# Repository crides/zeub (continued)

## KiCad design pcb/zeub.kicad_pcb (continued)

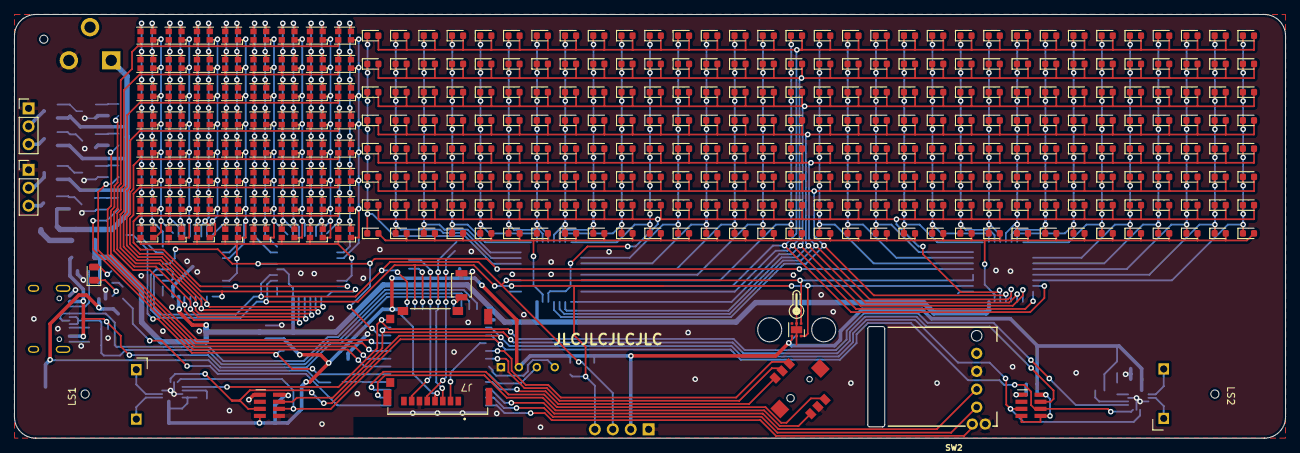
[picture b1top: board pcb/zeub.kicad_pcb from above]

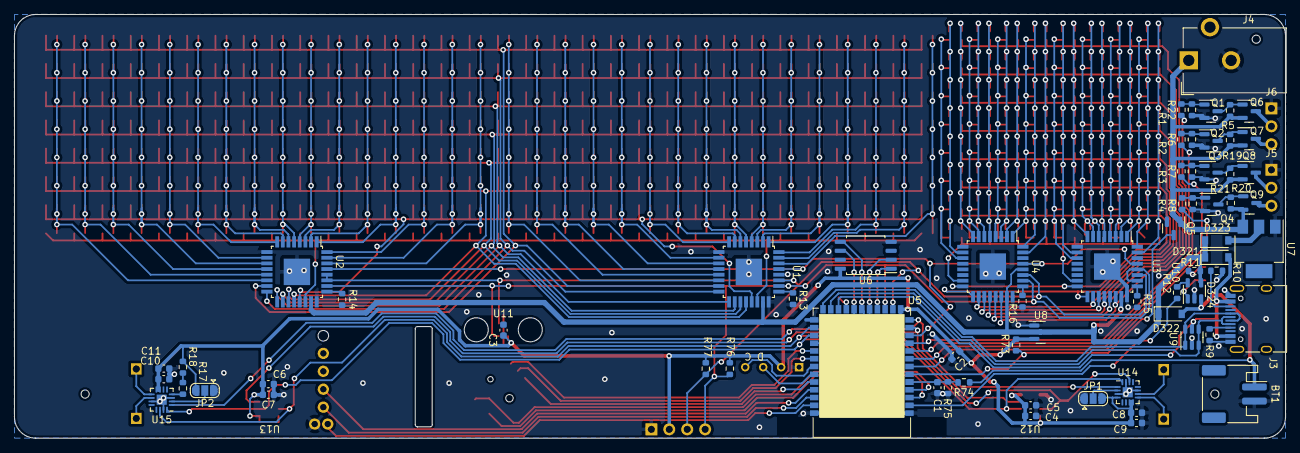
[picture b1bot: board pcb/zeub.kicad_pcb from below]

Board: 2 copper layers, 180.0 x 60.0 mm, 401 parts (68 on the bottom side), 140 nets.

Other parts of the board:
C4, C6: 10uF; C_0603_1608Metric
C5, C7: 0.1uF; C_0603_1608Metric
U12, U13: CMM4030D; CMM4030D_hand_solder

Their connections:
+3V3: C4.2, C5.2, C6.2, C7.2, U12.4 (EN), U12.8 (VDD), U13.4 (EN), U13.5 (~L/R), U13.8 (VDD); also elsewhere on the board
BCLK: U12.6 (SCK), U13.6 (SCK); also elsewhere on the board
GND: C4.1, C5.1, C6.1, C7.1, U12.1 (GND), U12.5 (~L/R), U13.1 (GND); also elsewhere on the board
LRCLK: U12.3 (WS), U13.3 (WS); also elsewhere on the board
SDIN: U12.7 (SD), U13.7 (SD); also elsewhere on the board

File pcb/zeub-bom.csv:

Comment,Designator,Footprint,LCSC Part #
white,"D196,D219,D218,D232,D151,D252,D87,D47,D178,D34,D247,D226,D224,D17,D203,D173,D122,D249,D159,D105,D213,D5,D185,D130,D223,D78,D82,D80,D192,D229,D33,D85,D141,D157,D106,D188,D212,D75,D97,D123,D107,D128,D124,D190,D177,D149,D231,D64,D246,D191,D95,D20,D15,D50,D8,D182,D139,D170,D99,D215,D186,D21,D176,D152,D146,D202,D84,D76,D255,D81,D132,D110,D58,D145,D28,D40,D91,D240,D13,D38,D180,D25,D169,D148,D245,D133,D57,D52,D125,D221,D204,D181,D239,D134,D94,D155,D115,D136,D137,D22,D129,D216,D201,D10,D193,D93,D230,D164,D111,D197,D61,D51,D241,D39,D127,D103,D194,D62,D4,D183,D98,D114,D256,D206,D77,D23,D236,D2,D89,D150,D187,D7,D120,D90,D69,D154,D79,D65,D83,D54,D117,D222,D119,D248,D67,D68,D43,D244,D121,D37,D220,D92,D53,D205,D36,D211,D199,D3,D243,D158,D214,D70,D30,D156,D160,D45,D210,D66,D162,D109,D166,D44,D104,D59,D12,D88,D147,D113,D250,D56,D254,D48,D165,D72,D71,D238,D73,D200,D237,D161,D74,D86,D126,D29,D46,D163,D131,D195,D171,D31,D233,D143,D26,D1,D41,D101,D19,D112,D27,D138,D234,D175,D18,D174,D168,D207,D11,D118,D16,D108,D225,D172,D184,D116,D242,D32,D63,D96,D102,D228,D49,D42,D153,D100,D140,D60,D14,D217,D179,D208,D35,D198,D55,D167,D253,D144,D209,D135,D9,D142,D227,D189,D24,D235,D6,D251",D_0603_1608Metric,
LED_BGRA,"D290,D263,D311,D301,D291,D268,D260,D277,D298,D280,D302,D312,D283,D292,D273,D282,D320,D261,D270,D262,D276,D319,D266,D274,D281,D297,D278,D287,D310,D315,D300,D318,D303,D265,D296,D286,D289,D272,D288,D294,D308,D285,D279,D293,D316,D259,D313,D258,D257,D269,D284,D275,D317,D295,D314,D271,D307,D267,D264,D309,D305,D306,D299,D304",LED_ASMB-KTF0-0A306,
CMM4030D,"U13,U12",CMM4030D_hand_solder,
Conn_01x03,"J5,J6",PinHeader_1x03_P2.54mm_Vertical,
SKRHA,SW1,SKRHA-boss,
LED,D324,D_0805_2012Metric,
TMP117,U11,WSON-6-1EP_2x2mm_P0.65mm_EP1x1.6mm,
Speaker,"LS2,LS1",CMS1609,
RotaryEncoder_Switch,SW2,EVQWGD001,
SW_Push,SW3,SW_SPST_B3U-1000P,
Micro_SD_Card_Det,J7,molex-503182-1852,
OLED-128x32,J2,OLED-128x64,
5.1k,"R10,R9",R_0603_1608Metric,
AO3400A,"Q4,Q1,Q5,Q2,Q3",SOT-23,
100,"R3,R2,R1,R4",R_0603_1608Metric,
MAX98357A,"U15,U14",QFN-16-1EP_3x3mm_P0.5mm_EP1.45x1.45mm,
10nF,C1,C_0603_1608Metric,
AO3401A,"Q6,Q9,Q7,Q8",SOT-23,
100k,"R18,R8,R22,R6,R7,R17,R73",R_0603_1608Metric,
SRV05-4,U9,SOT-23-6,
0.1uF,"C10,C7,C8,C3,C5",C_0603_1608Metric,
IS31FL3729,"U2,U1,U4,U3",eTQFP-32_7x7mm_P0.8mm,
10k,"R19,R12,R21,R20,R16,R5,R13,R14,R15",R_0603_1608Metric,
10uF,"C9,C4,C11,C6",C_0603_1608Metric,
2.2k,"R77,R76",R_0603_1608Metric,
SolderJumper_3_Open,"JP1,JP2",SolderJumper-3_P1.3mm_Open_RoundedPad1.0x1.5mm,
LTC4054ES5-4.2,U10,TSOT-23-5,
1k,R11,R_0603_1608Metric,
holyiot-18010-no-underside,U5,holyiot-18010-no-underside,
TLV1117-50,U7,SOT-223,
1uF,C2,C_0603_1608Metric,
USB_C_Receptacle_USB2.0,J3,USB_C_Receptacle_HRO_TYPE-C-31-M-12,
5.1M,"R75,R74",R_0603_1608Metric,
D_Schottky,"D323,D321,D322",D_SOD-123,
MT25QL128ABA1ESE,U6,SOIC-8_5.23x5.23mm_P1.27mm,
Barrel_Jack_Switch,J4,BarrelJack_CUI_PJ-102AH_Horizontal,
XC6206PxxxMR,U8,SOT-23,
Battery_Cell,BT1,JST_PH_S2B-PH-SM4-TB_1x02-1MP_P2.00mm_Horizontal,

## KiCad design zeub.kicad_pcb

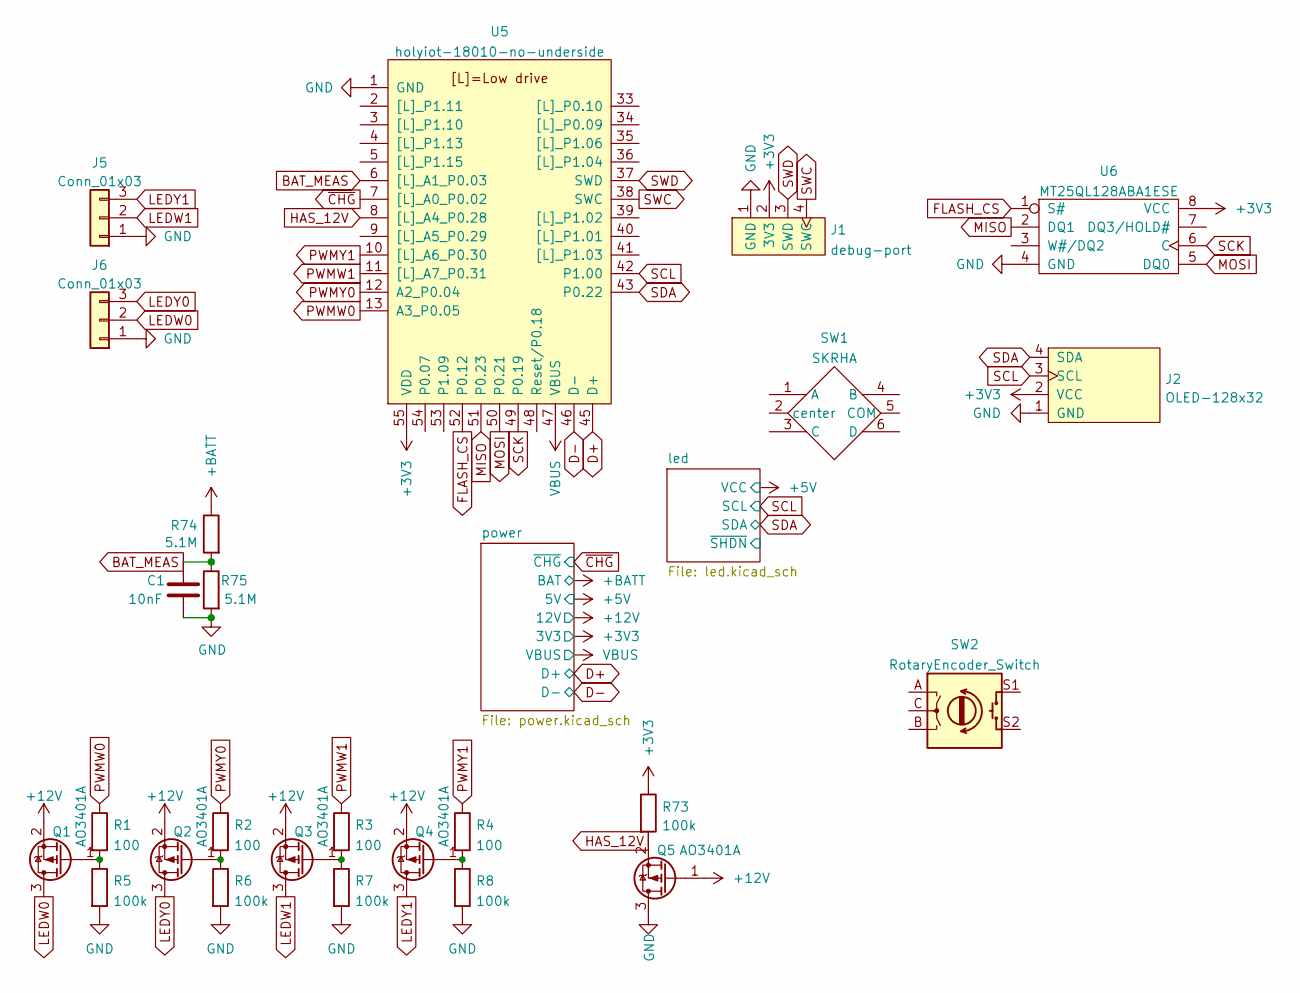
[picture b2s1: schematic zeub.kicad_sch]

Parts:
C1: 10nF; C_0603_1608Metric
J1: debug-port; debug-port-single-side
J2: OLED-128x32; OLED-128x32-cutout
J5, J6: Conn_01x03; PinHeader_1x03_P2.54mm_Vertical
Q1, Q2, Q3, Q4, Q5: AO3401A; SOT-23
R1, R2, R3, R4: 100; R_0603_1608Metric
R5, R6, R7, R8, R73: 100k; R_0603_1608Metric
R74, R75: 5.1M; R_0603_1608Metric
SW1: SKRHA; SKRHA-boss
SW2: RotaryEncoder_Switch; RotaryEncoder_Alps_EC12E-Switch_Vertical_H20mm_CircularMoun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
U5: holyiot-18010-no-underside
U6: MT25QL128ABA1ESE; SOIC-8_5.23x5.23mm_P1.27mm

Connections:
+3V3: J1.2 (3V3), J2.2 (VCC), R73.1, U5.55 (VDD), U6.8 (VCC); also elsewhere on the board
+12V: Q1.2 (S), Q2.2 (S), Q3.2 (S), Q4.2 (S), Q5.1 (G); also elsewhere on the board
+BATT: R74.1; also elsewhere on the board
BAT_MEAS: C1.1, R74.2, R75.1, U5.6 ([L]_A1_P0.03)
D+: U5.45 (D+); also elsewhere on the board
D-: U5.46 (D-); also elsewhere on the board
FLASH_CS: U5.52 (P0.12), U6.1 (S#)
GND: C1.2, J1.1 (GND), J2.1 (GND), J5.1, J6.1, Q5.3 (D), R5.2, R6.2, R7.2, R8.2, R75.2, U5.1 (GND), U5.32 (GND), U5.44 (GND), U6.4 (GND); also elsewhere on the board
HAS_12V: Q5.2 (S), R73.2, U5.8 ([L]_A4_P0.28)
LEDW0: J6.2, Q1.3 (D)
LEDW1: J5.2, Q3.3 (D)
LEDY0: J6.3, Q2.3 (D)
LEDY1: J5.3, Q4.3 (D)
MISO: U5.51 (P0.23), U6.2 (DQ1)
MOSI: U5.50 (P0.21), U6.5 (DQ0)
unnamed: Q1.1 (G), R1.2, R5.1
unnamed: Q2.1 (G), R2.2, R6.1
unnamed: Q3.1 (G), R3.2, R7.1
unnamed: Q4.1 (G), R4.2, R8.1
PWMW0: R1.1, U5.13 (A3_P0.05)
PWMW1: R3.1, U5.11 ([L]_A7_P0.31)
PWMY0: R2.1, U5.12 (A2_P0.04)
PWMY1: R4.1, U5.10 ([L]_A6_P0.30)
SCK: U5.49 (P0.19), U6.6 (C)
SCL: J2.3 (SCL), U5.42 (P1.00); also elsewhere on the board
SDA: J2.4 (SDA), U5.43 (P0.22); also elsewhere on the board
SWC: J1.4 (SWC), U5.38 (SWC)
SWD: J1.3 (SWD), U5.37 (SWD)
VBUS: U5.47 (VBUS); also elsewhere on the board
~CHG: U5.7 ([L]_A0_P0.02); also elsewhere on the board

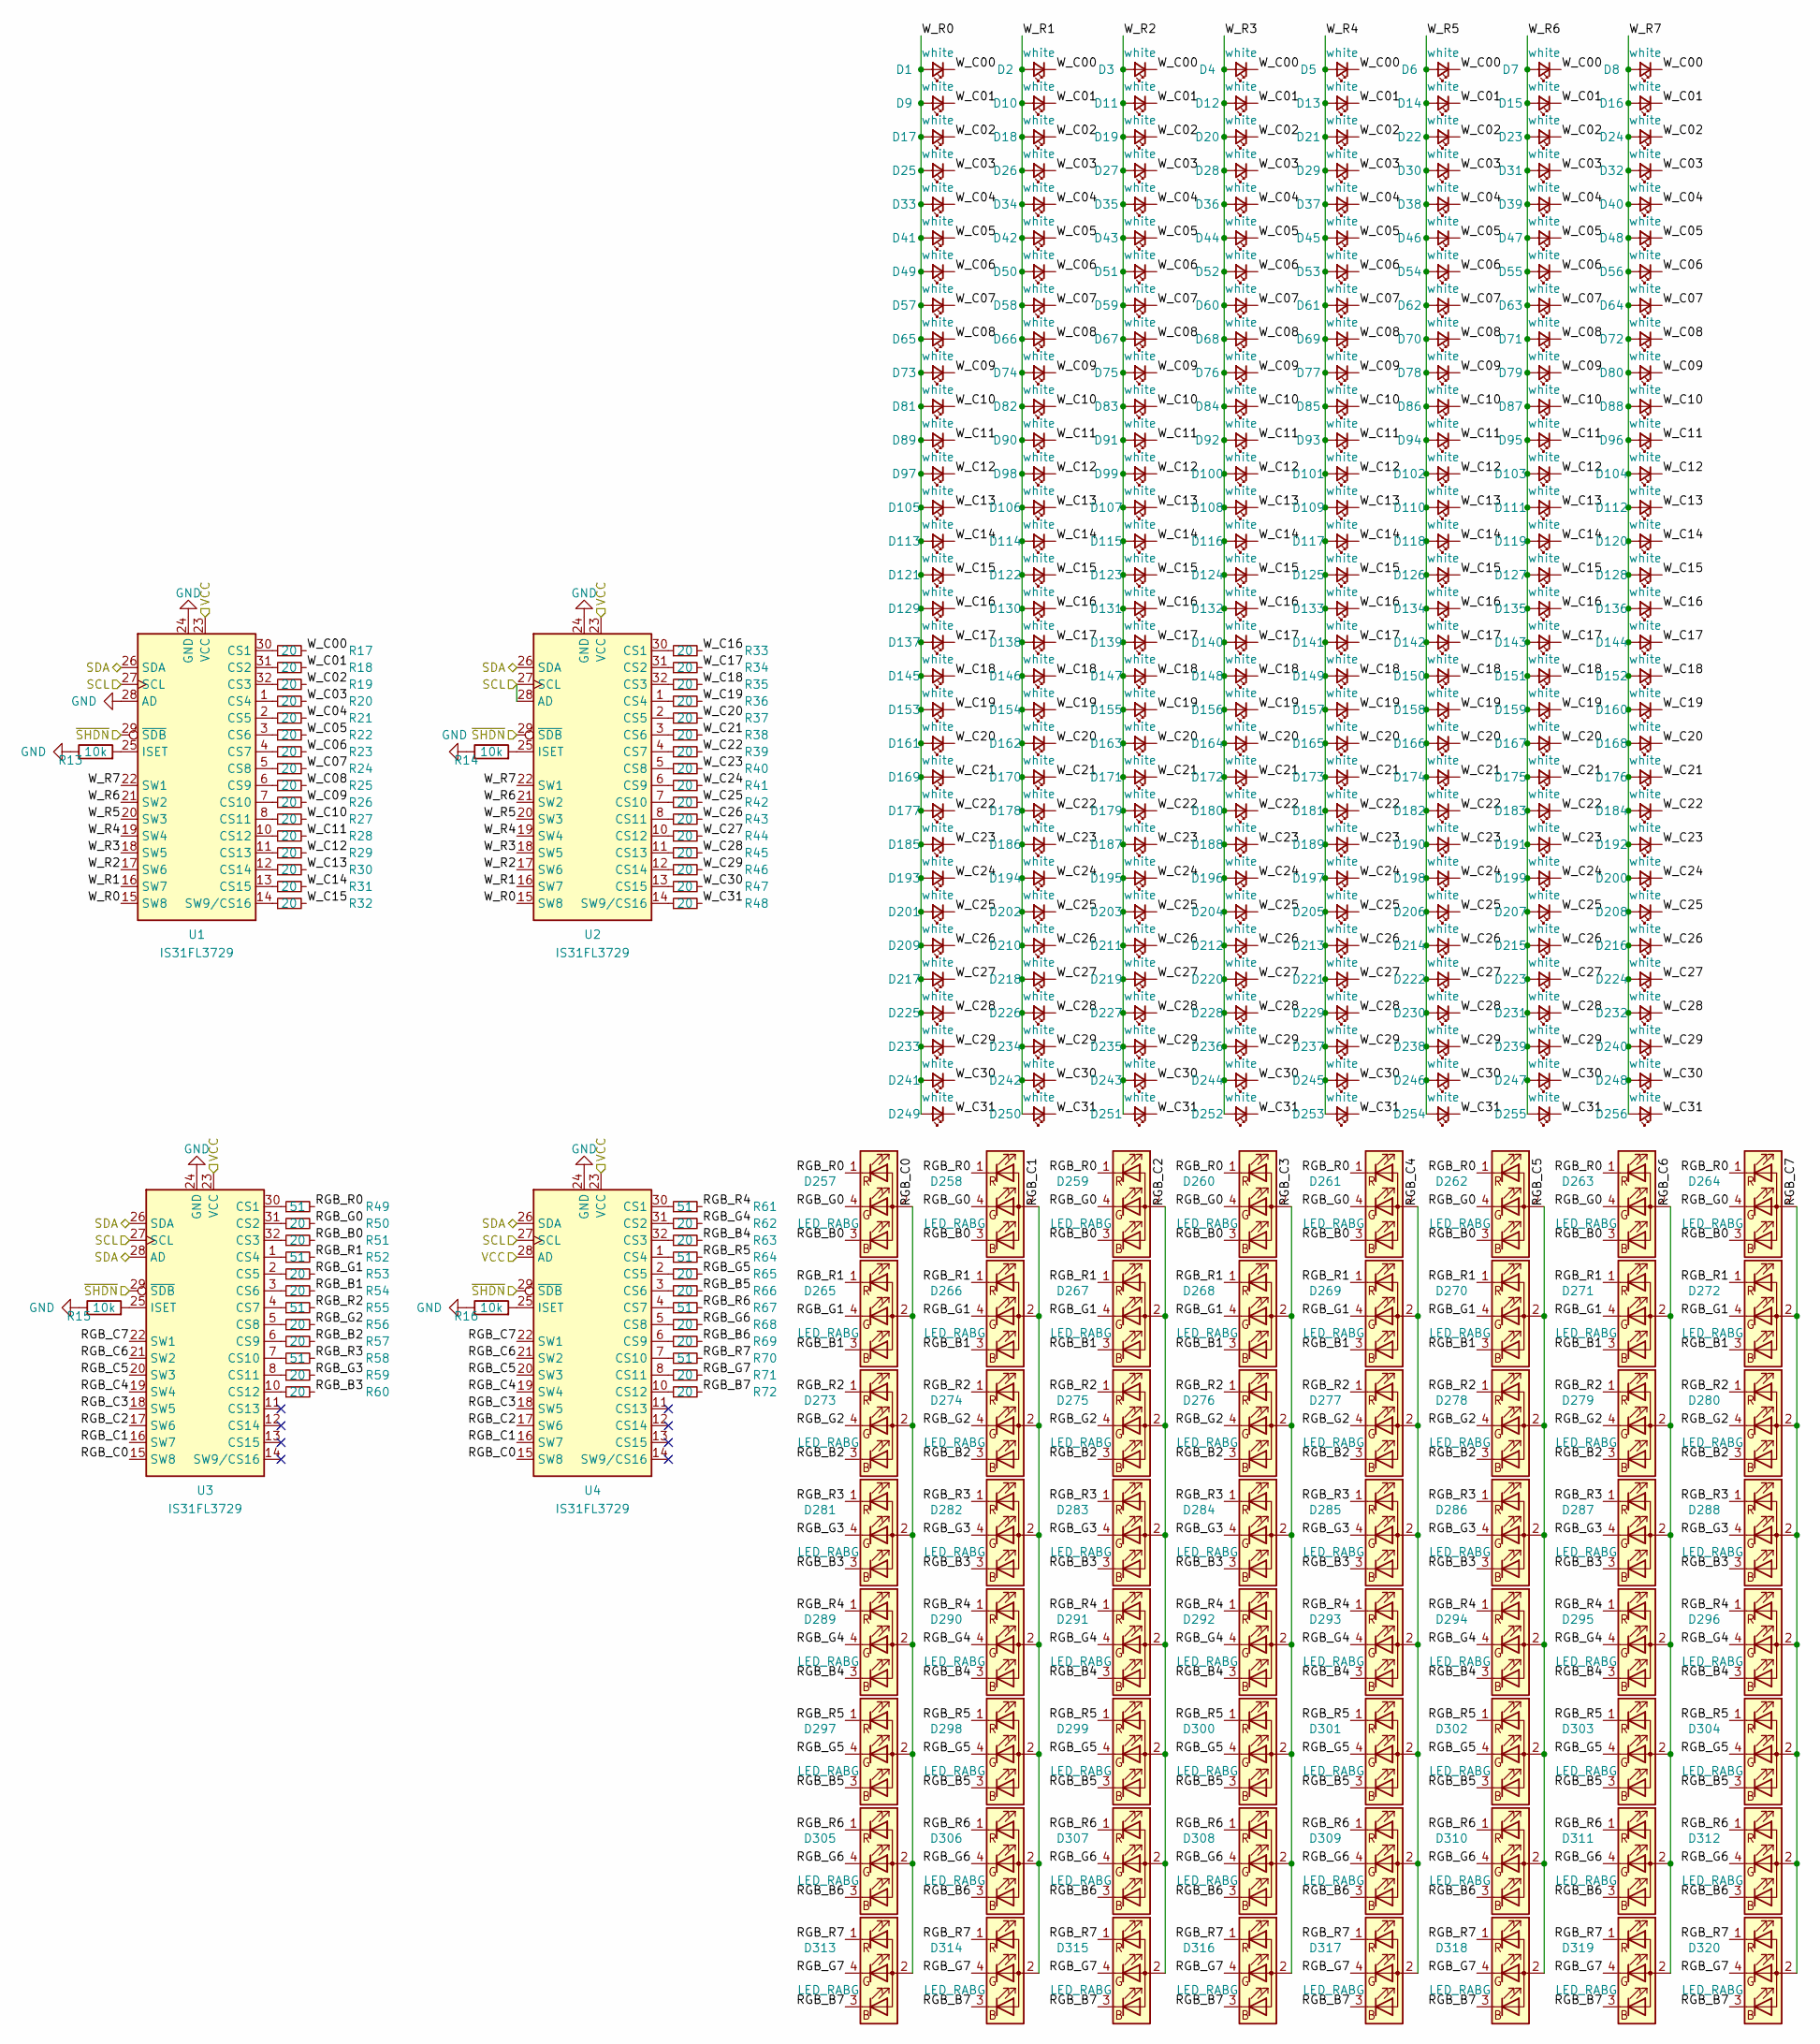
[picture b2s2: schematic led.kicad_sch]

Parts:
D1, D2, D3, D4, D5, D6, D7, D8, D9, D10, D11, D12, D13, D14, D15, D16, D17, D18, D19, D20, D21, D22, D23, D24, D25, D26, D27, D28, D29, D30, D31, D32, D33, D34, D35, D36, D37, D38, D39, D40, D41, D42, D43, D44, D45, D46, D47, D48, D49, D50, D51, D52, D53, D54, D55, D56, D57, D58, D59, D60, D61, D62, D63, D64, D65, D66, D67, D68, D69, D70, D71, D72, D73, D74, D75, D76, D77, D78, D79, D80, D81, D82, D83, D84, D85, D86, D87, D88, D89, D90, D91, D92, D93, D94, D95, D96, D97, D98, D99, D100, D101, D102, D103, D104, D105, D106, D107, D108, D109, D110, D111, D112, D113, D114, D115, D116, D117, D118, D119, D120, D121, D122, D123, D124, D125, D126, D127, D128, D129, D130, D131, D132, D133, D134, D135, D136, D137, D138, D139, D140, D141, D142, D143, D144, D145, D146, D147, D148, D149, D150, D151, D152, D153, D154, D155, D156, D157, D158, D159, D160, D161, D162, D163, D164, D165, D166, D167, D168, D169, D170, D171, D172, D173, D174, D175, D176, D177, D178, D179, D180, D181, D182, D183, D184, D185, D186, D187, D188, D189, D190, D191, D192, D193, D194, D195, D196, D197, D198, D199, D200, D201, D202, D203, D204, D205, D206, D207, D208, D209, D210, D211, D212, D213, D214, D215, D216, D217, D218, D219, D220, D221, D222, D223, D224, D225, D226, D227, D228, D229, D230, D231, D232, D233, D234, D235, D236, D237, D238, D239, D240, D241, D242, D243, D244, D245, D246, D247, D248, D249, D250, D251, D252, D253, D254, D255, D256: white; D_0603_1608Metric
D257, D258, D259, D260, D261, D262, D263, D264, D265, D266, D267, D268, D269, D270, D271, D272, D273, D274, D275, D276, D277, D278, D279, D280, D281, D282, D283, D284, D285, D286, D287, D288, D289, D290, D291, D292, D293, D294, D295, D296, D297, D298, D299, D300, D301, D302, D303, D304, D305, D306, D307, D308, D309, D310, D311, D312, D313, D314, D315, D316, D317, D318, D319, D320: LED_RABG; LED_ASMB-KTF0-0A306
R13, R14, R15, R16: 10k; R_0603_1608Metric
R17, R18, R19, R20, R21, R22, R23, R24, R25, R26, R27, R28, R29, R30, R31, R32, R33, R34, R35, R36, R37, R38, R39, R40, R41, R42, R43, R44, R45, R46, R47, R48, R50, R51, R53, R54, R56, R57, R59, R60, R62, R63, R65, R66, R68, R69, R71, R72: 20; R_0603_1608Metric
R49, R52, R55, R58, R61, R64, R67, R70: 51; R_0603_1608Metric
U1, U2, U3, U4: IS31FL3729; QFN-32-1EP_4x4mm_P0.4mm_EP2.9x2.9mm

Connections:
+5V: U1.23 (VCC), U2.23 (VCC), U3.23 (VCC), U4.23 (VCC), U4.28 (AD); also elsewhere on the board
/led/RGB_B0: D257.3 (BK), D258.3 (BK), D259.3 (BK), D260.3 (BK), D261.3 (BK), D262.3 (BK), D263.3 (BK), D264.3 (BK), R51.2
/led/RGB_B1: D265.3 (BK), D266.3 (BK), D267.3 (BK), D268.3 (BK), D269.3 (BK), D270.3 (BK), D271.3 (BK), D272.3 (BK), R54.2
/led/RGB_B2: D273.3 (BK), D274.3 (BK), D275.3 (BK), D276.3 (BK), D277.3 (BK), D278.3 (BK), D279.3 (BK), D280.3 (BK), R57.2
/led/RGB_B3: D281.3 (BK), D282.3 (BK), D283.3 (BK), D284.3 (BK), D285.3 (BK), D286.3 (BK), D287.3 (BK), D288.3 (BK), R60.2
/led/RGB_B4: D289.3 (BK), D290.3 (BK), D291.3 (BK), D292.3 (BK), D293.3 (BK), D294.3 (BK), D295.3 (BK), D296.3 (BK), R63.2
/led/RGB_B5: D297.3 (BK), D298.3 (BK), D299.3 (BK), D300.3 (BK), D301.3 (BK), D302.3 (BK), D303.3 (BK), D304.3 (BK), R66.2
/led/RGB_B6: D305.3 (BK), D306.3 (BK), D307.3 (BK), D308.3 (BK), D309.3 (BK), D310.3 (BK), D311.3 (BK), D312.3 (BK), R69.2
/led/RGB_B7: D313.3 (BK), D314.3 (BK), D315.3 (BK), D316.3 (BK), D317.3 (BK), D318.3 (BK), D319.3 (BK), D320.3 (BK), R72.2
/led/RGB_C0: D257.2 (A), D265.2 (A), D273.2 (A), D281.2 (A), D289.2 (A), D297.2 (A), D305.2 (A), D313.2 (A), U3.15 (SW8), U4.15 (SW8)
/led/RGB_C1: D258.2 (A), D266.2 (A), D274.2 (A), D282.2 (A), D290.2 (A), D298.2 (A), D306.2 (A), D314.2 (A), U3.16 (SW7), U4.16 (SW7)
/led/RGB_C2: D259.2 (A), D267.2 (A), D275.2 (A), D283.2 (A), D291.2 (A), D299.2 (A), D307.2 (A), D315.2 (A), U3.17 (SW6), U4.17 (SW6)
/led/RGB_C3: D260.2 (A), D268.2 (A), D276.2 (A), D284.2 (A), D292.2 (A), D300.2 (A), D308.2 (A), D316.2 (A), U3.18 (SW5), U4.18 (SW5)
/led/RGB_C4: D261.2 (A), D269.2 (A), D277.2 (A), D285.2 (A), D293.2 (A), D301.2 (A), D309.2 (A), D317.2 (A), U3.19 (SW4), U4.19 (SW4)
/led/RGB_C5: D262.2 (A), D270.2 (A), D278.2 (A), D286.2 (A), D294.2 (A), D302.2 (A), D310.2 (A), D318.2 (A), U3.20 (SW3), U4.20 (SW3)
/led/RGB_C6: D263.2 (A), D271.2 (A), D279.2 (A), D287.2 (A), D295.2 (A), D303.2 (A), D311.2 (A), D319.2 (A), U3.21 (SW2), U4.21 (SW2)
/led/RGB_C7: D264.2 (A), D272.2 (A), D280.2 (A), D288.2 (A), D296.2 (A), D304.2 (A), D312.2 (A), D320.2 (A), U3.22 (SW1), U4.22 (SW1)
/led/RGB_G0: D257.4 (GK), D258.4 (GK), D259.4 (GK), D260.4 (GK), D261.4 (GK), D262.4 (GK), D263.4 (GK), D264.4 (GK), R50.2
/led/RGB_G1: D265.4 (GK), D266.4 (GK), D267.4 (GK), D268.4 (GK), D269.4 (GK), D270.4 (GK), D271.4 (GK), D272.4 (GK), R53.2
/led/RGB_G2: D273.4 (GK), D274.4 (GK), D275.4 (GK), D276.4 (GK), D277.4 (GK), D278.4 (GK), D279.4 (GK), D280.4 (GK), R56.2
/led/RGB_G3: D281.4 (GK), D282.4 (GK), D283.4 (GK), D284.4 (GK), D285.4 (GK), D286.4 (GK), D287.4 (GK), D288.4 (GK), R59.2
/led/RGB_G4: D289.4 (GK), D290.4 (GK), D291.4 (GK), D292.4 (GK), D293.4 (GK), D294.4 (GK), D295.4 (GK), D296.4 (GK), R62.2
/led/RGB_G5: D297.4 (GK), D298.4 (GK), D299.4 (GK), D300.4 (GK), D301.4 (GK), D302.4 (GK), D303.4 (GK), D304.4 (GK), R65.2
/led/RGB_G6: D305.4 (GK), D306.4 (GK), D307.4 (GK), D308.4 (GK), D309.4 (GK), D310.4 (GK), D311.4 (GK), D312.4 (GK), R68.2
/led/RGB_G7: D313.4 (GK), D314.4 (GK), D315.4 (GK), D316.4 (GK), D317.4 (GK), D318.4 (GK), D319.4 (GK), D320.4 (GK), R71.2
/led/RGB_R0: D257.1 (RK), D258.1 (RK), D259.1 (RK), D260.1 (RK), D261.1 (RK), D262.1 (RK), D263.1 (RK), D264.1 (RK), R49.2
/led/RGB_R1: D265.1 (RK), D266.1 (RK), D267.1 (RK), D268.1 (RK), D269.1 (RK), D270.1 (RK), D271.1 (RK), D272.1 (RK), R52.2
/led/RGB_R2: D273.1 (RK), D274.1 (RK), D275.1 (RK), D276.1 (RK), D277.1 (RK), D278.1 (RK), D279.1 (RK), D280.1 (RK), R55.2
/led/RGB_R3: D281.1 (RK), D282.1 (RK), D283.1 (RK), D284.1 (RK), D285.1 (RK), D286.1 (RK), D287.1 (RK), D288.1 (RK), R58.2
/led/RGB_R4: D289.1 (RK), D290.1 (RK), D291.1 (RK), D292.1 (RK), D293.1 (RK), D294.1 (RK), D295.1 (RK), D296.1 (RK), R61.2
/led/RGB_R5: D297.1 (RK), D298.1 (RK), D299.1 (RK), D300.1 (RK), D301.1 (RK), D302.1 (RK), D303.1 (RK), D304.1 (RK), R64.2
/led/RGB_R6: D305.1 (RK), D306.1 (RK), D307.1 (RK), D308.1 (RK), D309.1 (RK), D310.1 (RK), D311.1 (RK), D312.1 (RK), R67.2
/led/RGB_R7: D313.1 (RK), D314.1 (RK), D315.1 (RK), D316.1 (RK), D317.1 (RK), D318.1 (RK), D319.1 (RK), D320.1 (RK), R70.2
/led/W_C00: D1.1 (K), D2.1 (K), D3.1 (K), D4.1 (K), D5.1 (K), D6.1 (K), D7.1 (K), D8.1 (K), R17.2
/led/W_C01: D9.1 (K), D10.1 (K), D11.1 (K), D12.1 (K), D13.1 (K), D14.1 (K), D15.1 (K), D16.1 (K), R18.2
/led/W_C02: D17.1 (K), D18.1 (K), D19.1 (K), D20.1 (K), D21.1 (K), D22.1 (K), D23.1 (K), D24.1 (K), R19.2
/led/W_C03: D25.1 (K), D26.1 (K), D27.1 (K), D28.1 (K), D29.1 (K), D30.1 (K), D31.1 (K), D32.1 (K), R20.2
/led/W_C04: D33.1 (K), D34.1 (K), D35.1 (K), D36.1 (K), D37.1 (K), D38.1 (K), D39.1 (K), D40.1 (K), R21.2
/led/W_C05: D41.1 (K), D42.1 (K), D43.1 (K), D44.1 (K), D45.1 (K), D46.1 (K), D47.1 (K), D48.1 (K), R22.2
/led/W_C06: D49.1 (K), D50.1 (K), D51.1 (K), D52.1 (K), D53.1 (K), D54.1 (K), D55.1 (K), D56.1 (K), R23.2
/led/W_C07: D57.1 (K), D58.1 (K), D59.1 (K), D60.1 (K), D61.1 (K), D62.1 (K), D63.1 (K), D64.1 (K), R24.2
/led/W_C08: D65.1 (K), D66.1 (K), D67.1 (K), D68.1 (K), D69.1 (K), D70.1 (K), D71.1 (K), D72.1 (K), R25.2
/led/W_C09: D73.1 (K), D74.1 (K), D75.1 (K), D76.1 (K), D77.1 (K), D78.1 (K), D79.1 (K), D80.1 (K), R26.2
/led/W_C10: D81.1 (K), D82.1 (K), D83.1 (K), D84.1 (K), D85.1 (K), D86.1 (K), D87.1 (K), D88.1 (K), R27.2
/led/W_C11: D89.1 (K), D90.1 (K), D91.1 (K), D92.1 (K), D93.1 (K), D94.1 (K), D95.1 (K), D96.1 (K), R28.2
/led/W_C12: D97.1 (K), D98.1 (K), D99.1 (K), D100.1 (K), D101.1 (K), D102.1 (K), D103.1 (K), D104.1 (K), R29.2
/led/W_C13: D105.1 (K), D106.1 (K), D107.1 (K), D108.1 (K), D109.1 (K), D110.1 (K), D111.1 (K), D112.1 (K), R30.2
/led/W_C14: D113.1 (K), D114.1 (K), D115.1 (K), D116.1 (K), D117.1 (K), D118.1 (K), D119.1 (K), D120.1 (K), R31.2
/led/W_C15: D121.1 (K), D122.1 (K), D123.1 (K), D124.1 (K), D125.1 (K), D126.1 (K), D127.1 (K), D128.1 (K), R32.2
/led/W_C16: D129.1 (K), D130.1 (K), D131.1 (K), D132.1 (K), D133.1 (K), D134.1 (K), D135.1 (K), D136.1 (K), R33.2
/led/W_C17: D137.1 (K), D138.1 (K), D139.1 (K), D140.1 (K), D141.1 (K), D142.1 (K), D143.1 (K), D144.1 (K), R34.2
/led/W_C18: D145.1 (K), D146.1 (K), D147.1 (K), D148.1 (K), D149.1 (K), D150.1 (K), D151.1 (K), D152.1 (K), R35.2
/led/W_C19: D153.1 (K), D154.1 (K), D155.1 (K), D156.1 (K), D157.1 (K), D158.1 (K), D159.1 (K), D160.1 (K), R36.2
/led/W_C20: D161.1 (K), D162.1 (K), D163.1 (K), D164.1 (K), D165.1 (K), D166.1 (K), D167.1 (K), D168.1 (K), R37.2
/led/W_C21: D169.1 (K), D170.1 (K), D171.1 (K), D172.1 (K), D173.1 (K), D174.1 (K), D175.1 (K), D176.1 (K), R38.2
/led/W_C22: D177.1 (K), D178.1 (K), D179.1 (K), D180.1 (K), D181.1 (K), D182.1 (K), D183.1 (K), D184.1 (K), R39.2
/led/W_C23: D185.1 (K), D186.1 (K), D187.1 (K), D188.1 (K), D189.1 (K), D190.1 (K), D191.1 (K), D192.1 (K), R40.2
/led/W_C24: D193.1 (K), D194.1 (K), D195.1 (K), D196.1 (K), D197.1 (K), D198.1 (K), D199.1 (K), D200.1 (K), R41.2
/led/W_C25: D201.1 (K), D202.1 (K), D203.1 (K), D204.1 (K), D205.1 (K), D206.1 (K), D207.1 (K), D208.1 (K), R42.2
/led/W_C26: D209.1 (K), D210.1 (K), D211.1 (K), D212.1 (K), D213.1 (K), D214.1 (K), D215.1 (K), D216.1 (K), R43.2
/led/W_C27: D217.1 (K), D218.1 (K), D219.1 (K), D220.1 (K), D221.1 (K), D222.1 (K), D223.1 (K), D224.1 (K), R44.2
/led/W_C28: D225.1 (K), D226.1 (K), D227.1 (K), D228.1 (K), D229.1 (K), D230.1 (K), D231.1 (K), D232.1 (K), R45.2
/led/W_C29: D233.1 (K), D234.1 (K), D235.1 (K), D236.1 (K), D237.1 (K), D238.1 (K), D239.1 (K), D240.1 (K), R46.2
/led/W_C30: D241.1 (K), D242.1 (K), D243.1 (K), D244.1 (K), D245.1 (K), D246.1 (K), D247.1 (K), D248.1 (K), R47.2
/led/W_C31: D249.1 (K), D250.1 (K), D251.1 (K), D252.1 (K), D253.1 (K), D254.1 (K), D255.1 (K), D256.1 (K), R48.2
/led/W_R0: D1.2 (A), D9.2 (A), D17.2 (A), D25.2 (A), D33.2 (A), D41.2 (A), D49.2 (A), D57.2 (A), D65.2 (A), D73.2 (A), D81.2 (A), D89.2 (A), D97.2 (A), D105.2 (A), D113.2 (A), D121.2 (A), D129.2 (A), D137.2 (A), D145.2 (A), D153.2 (A), D161.2 (A), D169.2 (A), D177.2 (A), D185.2 (A), D193.2 (A), D201.2 (A), D209.2 (A), D217.2 (A), D225.2 (A), D233.2 (A), D241.2 (A), D249.2 (A), U1.15 (SW8), U2.15 (SW8)
/led/W_R1: D2.2 (A), D10.2 (A), D18.2 (A), D26.2 (A), D34.2 (A), D42.2 (A), D50.2 (A), D58.2 (A), D66.2 (A), D74.2 (A), D82.2 (A), D90.2 (A), D98.2 (A), D106.2 (A), D114.2 (A), D122.2 (A), D130.2 (A), D138.2 (A), D146.2 (A), D154.2 (A), D162.2 (A), D170.2 (A), D178.2 (A), D186.2 (A), D194.2 (A), D202.2 (A), D210.2 (A), D218.2 (A), D226.2 (A), D234.2 (A), D242.2 (A), D250.2 (A), U1.16 (SW7), U2.16 (SW7)
/led/W_R2: D3.2 (A), D11.2 (A), D19.2 (A), D27.2 (A), D35.2 (A), D43.2 (A), D51.2 (A), D59.2 (A), D67.2 (A), D75.2 (A), D83.2 (A), D91.2 (A), D99.2 (A), D107.2 (A), D115.2 (A), D123.2 (A), D131.2 (A), D139.2 (A), D147.2 (A), D155.2 (A), D163.2 (A), D171.2 (A), D179.2 (A), D187.2 (A), D195.2 (A), D203.2 (A), D211.2 (A), D219.2 (A), D227.2 (A), D235.2 (A), D243.2 (A), D251.2 (A), U1.17 (SW6), U2.17 (SW6)
/led/W_R3: D4.2 (A), D12.2 (A), D20.2 (A), D28.2 (A), D36.2 (A), D44.2 (A), D52.2 (A), D60.2 (A), D68.2 (A), D76.2 (A), D84.2 (A), D92.2 (A), D100.2 (A), D108.2 (A), D116.2 (A), D124.2 (A), D132.2 (A), D140.2 (A), D148.2 (A), D156.2 (A), D164.2 (A), D172.2 (A), D180.2 (A), D188.2 (A), D196.2 (A), D204.2 (A), D212.2 (A), D220.2 (A), D228.2 (A), D236.2 (A), D244.2 (A), D252.2 (A), U1.18 (SW5), U2.18 (SW5)
/led/W_R4: D5.2 (A), D13.2 (A), D21.2 (A), D29.2 (A), D37.2 (A), D45.2 (A), D53.2 (A), D61.2 (A), D69.2 (A), D77.2 (A), D85.2 (A), D93.2 (A), D101.2 (A), D109.2 (A), D117.2 (A), D125.2 (A), D133.2 (A), D141.2 (A), D149.2 (A), D157.2 (A), D165.2 (A), D173.2 (A), D181.2 (A), D189.2 (A), D197.2 (A), D205.2 (A), D213.2 (A), D221.2 (A), D229.2 (A), D237.2 (A), D245.2 (A), D253.2 (A), U1.19 (SW4), U2.19 (SW4)
/led/W_R5: D6.2 (A), D14.2 (A), D22.2 (A), D30.2 (A), D38.2 (A), D46.2 (A), D54.2 (A), D62.2 (A), D70.2 (A), D78.2 (A), D86.2 (A), D94.2 (A), D102.2 (A), D110.2 (A), D118.2 (A), D126.2 (A), D134.2 (A), D142.2 (A), D150.2 (A), D158.2 (A), D166.2 (A), D174.2 (A), D182.2 (A), D190.2 (A), D198.2 (A), D206.2 (A), D214.2 (A), D222.2 (A), D230.2 (A), D238.2 (A), D246.2 (A), D254.2 (A), U1.20 (SW3), U2.20 (SW3)
/led/W_R6: D7.2 (A), D15.2 (A), D23.2 (A), D31.2 (A), D39.2 (A), D47.2 (A), D55.2 (A), D63.2 (A), D71.2 (A), D79.2 (A), D87.2 (A), D95.2 (A), D103.2 (A), D111.2 (A), D119.2 (A), D127.2 (A), D135.2 (A), D143.2 (A), D151.2 (A), D159.2 (A), D167.2 (A), D175.2 (A), D183.2 (A), D191.2 (A), D199.2 (A), D207.2 (A), D215.2 (A), D223.2 (A), D231.2 (A), D239.2 (A), D247.2 (A), D255.2 (A), U1.21 (SW2), U2.21 (SW2)
/led/W_R7: D8.2 (A), D16.2 (A), D24.2 (A), D32.2 (A), D40.2 (A), D48.2 (A), D56.2 (A), D64.2 (A), D72.2 (A), D80.2 (A), D88.2 (A), D96.2 (A), D104.2 (A), D112.2 (A), D120.2 (A), D128.2 (A), D136.2 (A), D144.2 (A), D152.2 (A), D160.2 (A), D168.2 (A), D176.2 (A), D184.2 (A), D192.2 (A), D200.2 (A), D208.2 (A), D216.2 (A), D224.2 (A), D232.2 (A), D240.2 (A), D248.2 (A), D256.2 (A), U1.22 (SW1), U2.22 (SW1)
/led/~SHDN: U1.29 (~SDB), U2.29 (~SDB), U3.29 (~SDB), U4.29 (~SDB)
GND: R13.1, R14.1, R15.1, R16.1, U1.9 (GND), U1.24 (GND), U1.28 (AD), U1.33 (GND), U2.9 (GND), U2.24 (GND), U2.33 (GND), U3.9 (GND), U3.24 (GND), U3.33 (GND), U4.9 (GND), U4.24 (GND), U4.33 (GND); also elsewhere on the board
unnamed: R13.2, U1.25 (ISET)
unnamed: R14.2, U2.25 (ISET)
unnamed: R15.2, U3.25 (ISET)
unnamed: R16.2, U4.25 (ISET)
unnamed: R20.1, U1.1 (CS4)
unnamed: R21.1, U1.2 (CS5)
unnamed: R22.1, U1.3 (CS6)
unnamed: R23.1, U1.4 (CS7)
unnamed: R24.1, U1.5 (CS8)
unnamed: R25.1, U1.6 (CS9)
unnamed: R26.1, U1.7 (CS10)
unnamed: R27.1, U1.8 (CS11)
unnamed: R28.1, U1.10 (CS12)
unnamed: R29.1, U1.11 (CS13)
unnamed: R30.1, U1.12 (CS14)
unnamed: R31.1, U1.13 (CS15)
unnamed: R32.1, U1.14 (SW9/CS16)
unnamed: R17.1, U1.30 (CS1)
unnamed: R18.1, U1.31 (CS2)
unnamed: R19.1, U1.32 (CS3)
unnamed: R36.1, U2.1 (CS4)
unnamed: R37.1, U2.2 (CS5)
unnamed: R38.1, U2.3 (CS6)
unnamed: R39.1, U2.4 (CS7)
unnamed: R40.1, U2.5 (CS8)
unnamed: R41.1, U2.6 (CS9)
unnamed: R42.1, U2.7 (CS10)
unnamed: R43.1, U2.8 (CS11)
unnamed: R44.1, U2.10 (CS12)
unnamed: R45.1, U2.11 (CS13)
unnamed: R46.1, U2.12 (CS14)
unnamed: R47.1, U2.13 (CS15)
unnamed: R48.1, U2.14 (SW9/CS16)
unnamed: R33.1, U2.30 (CS1)
unnamed: R34.1, U2.31 (CS2)
unnamed: R35.1, U2.32 (CS3)
unnamed: R52.1, U3.1 (CS4)
unnamed: R53.1, U3.2 (CS5)
unnamed: R54.1, U3.3 (CS6)
unnamed: R55.1, U3.4 (CS7)
unnamed: R56.1, U3.5 (CS8)
unnamed: R57.1, U3.6 (CS9)
unnamed: R58.1, U3.7 (CS10)
unnamed: R59.1, U3.8 (CS11)
unnamed: R60.1, U3.10 (CS12)
unnamed: R49.1, U3.30 (CS1)
unnamed: R50.1, U3.31 (CS2)
unnamed: R51.1, U3.32 (CS3)
unnamed: R64.1, U4.1 (CS4)
unnamed: R65.1, U4.2 (CS5)
unnamed: R66.1, U4.3 (CS6)
unnamed: R67.1, U4.4 (CS7)
unnamed: R68.1, U4.5 (CS8)
unnamed: R69.1, U4.6 (CS9)
unnamed: R70.1, U4.7 (CS10)
unnamed: R71.1, U4.8 (CS11)
unnamed: R72.1, U4.10 (CS12)
unnamed: R61.1, U4.30 (CS1)
unnamed: R62.1, U4.31 (CS2)
unnamed: R63.1, U4.32 (CS3)
SCL: U1.27 (SCL), U2.27 (SCL), U2.28 (AD), U3.27 (SCL), U4.27 (SCL); also elsewhere on the board
SDA: U1.26 (SDA), U2.26 (SDA), U3.26 (SDA), U3.28 (AD), U4.26 (SDA); also elsewhere on the board

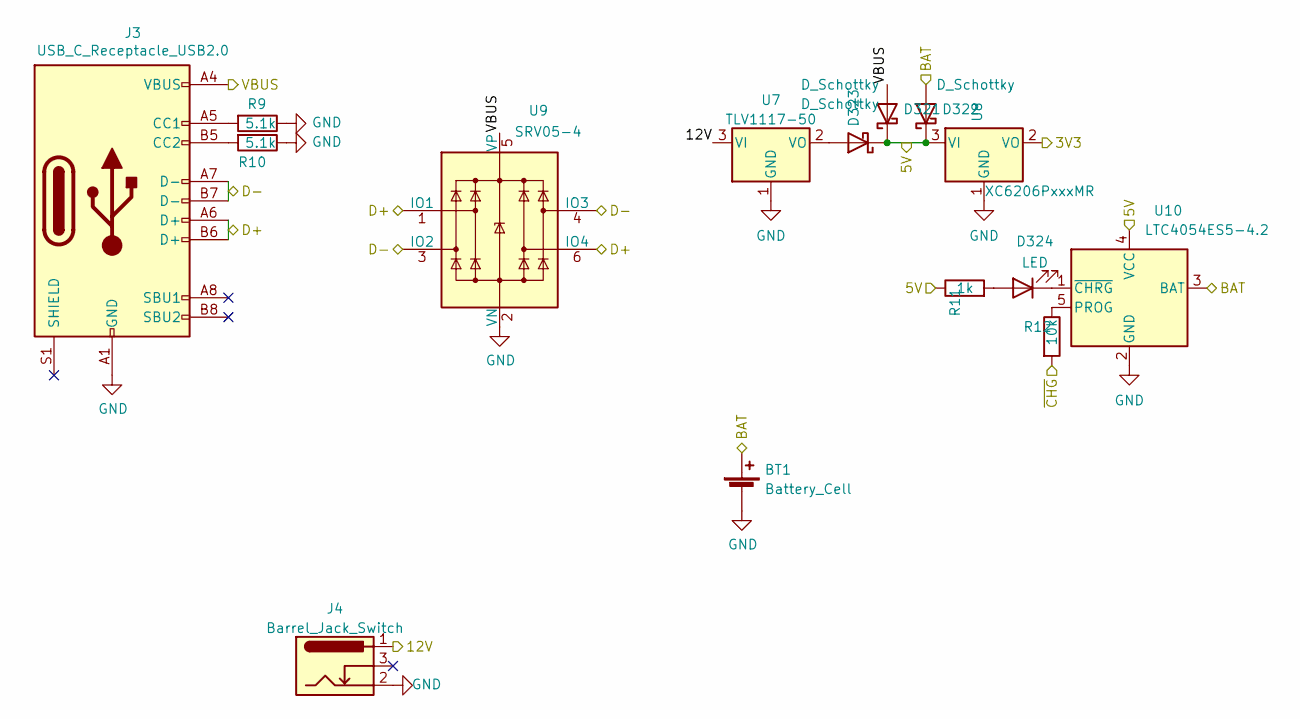
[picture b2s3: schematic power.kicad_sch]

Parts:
BT1: Battery_Cell; JST_PH_S2B-PH-SM4-TB_1x02-1MP_P2.00mm_Horizontal
D321, D322, D323: D_Schottky; D_SOD-123
D324: LED; D_0805_2012Metric
J3: USB_C_Receptacle_USB2.0; USB_C_Receptacle_HRO_TYPE-C-31-M-12
J4: Barrel_Jack_Switch; BarrelJack_CUI_PJ-102AH_Horizontal
R9, R10: 5.1k; R_0603_1608Metric
R11: 1k; R_0603_1608Metric
R12: 10k; R_0603_1608Metric
U7: TLV1117-50; SOT-223
U8: XC6206PxxxMR; SOT-23
U9: SRV05-4; SOT-23-6
U10: LTC4054ES5-4.2; TSOT-23-5

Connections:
+3V3: U8.2 (VO); also elsewhere on the board
+5V: D321.1 (K), D322.1 (K), D323.1 (K), R11.1, U8.3 (VI), U10.4 (VCC); also elsewhere on the board
+12V: J4.1, U7.3 (VI); also elsewhere on the board
+BATT: BT1.1 (+), D322.2 (A), U10.3 (BAT); also elsewhere on the board
D+: J3.A6 (D+), J3.B6 (D+), U9.1 (IO1), U9.6 (IO4); also elsewhere on the board
D-: J3.A7 (D-), J3.B7 (D-), U9.3 (IO2), U9.4 (IO3); also elsewhere on the board
GND: BT1.2 (-), J3.A1 (GND), J3.A12 (GND), J3.B1 (GND), J3.B12 (GND), J4.2, R9.1, R10.1, U7.1 (GND), U8.1 (GND), U9.2 (VN), U10.2 (GND); also elsewhere on the board
unnamed: D323.2 (A), U7.2 (VO)
unnamed: D324.1 (K), U10.1 (~CHRG)
unnamed: D324.2 (A), R11.2
unnamed: J3.A5 (CC1), R9.2
unnamed: J3.B5 (CC2), R10.2
unnamed: R12.1, U10.5 (PROG)
VBUS: D321.2 (A), J3.A4 (VBUS), J3.A9 (VBUS), J3.B4 (VBUS), J3.B9 (VBUS), U9.5 (VP); also elsewhere on the board
~CHG: R12.2; also elsewhere on the board

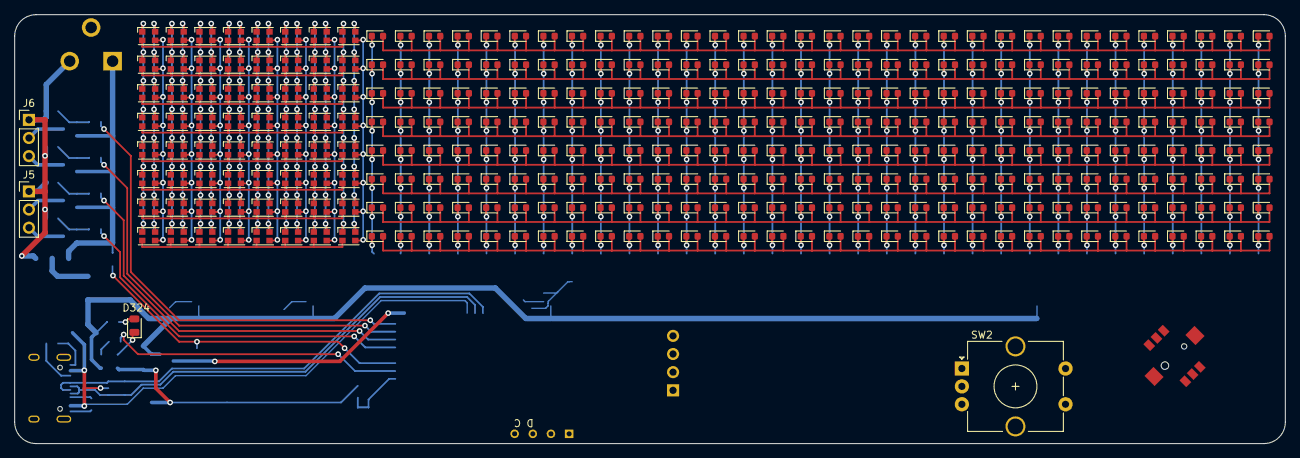
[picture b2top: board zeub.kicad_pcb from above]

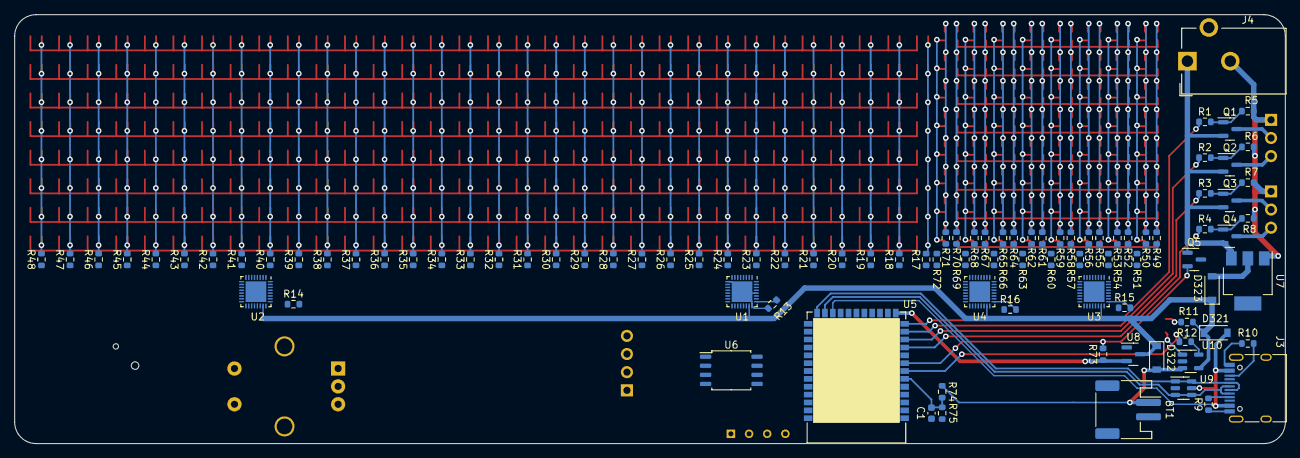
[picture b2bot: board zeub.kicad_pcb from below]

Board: 2 copper layers, 177.8 x 60.0 mm, 424 parts (65 on the bottom side), 170 nets.

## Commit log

2022-03-28 routed RGB
2022-03-28 routed matrix + PWM driver
2022-03-28 routed all LED + PMU
2022-03-28 routed PMU + rull RGB
2022-03-28 first version
2022-03-28 routed whites
2022-03-28 fully routed
2022-03-28 Added audio stuff; rerouted for prep
2022-03-28 routed PMU
2022-03-28 rid of LED driver resistors
2022-05-16 pcb: move into own directory
2022-05-28 firmware: simple light strip adjustment
2022-05-31 backup
2022-05-31 3D models
2022-05-31 simple temp display
2022-05-31 stupid clock with CTS
2023-03-11 f; zephyr 3.4
2023-03-13 stamp ground vias; ERC
2023-03-16 v2 fabbed
2023-03-26 pend: shell
2023-03-26 modified minecraft font from minecraftmono
2023-03-26 add is31fl3741 driver
    from https://github.com/zmkfirmware/zmk/pull/866
2023-03-28 firmware: zeub v2: simple clock icon and time on led matrix
2023-03-28 audio test
2023-04-06 fix audio
    - use big buffer for streaming
    - correct sampling rate
2023-04-06 add pics and README
